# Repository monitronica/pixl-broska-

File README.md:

# Pixl Broška — A Wearable Programmable Pixel Brooch

**A project by monitronica**

> Twenty LEDs, one tiny microcontroller, and a wearable space for words, images, and motion.

Official project visuals: [finished brooch and circuit-board close-up](https://radiona.org/monika-pocrnjic-radionica-pikslbroska/) · [workshop documentation](https://kons-platforma.org/en/dogodki/pixelbrooch-6/)

The official sources do not state a reusable image license, so photographs are linked rather than copied. See [image credits and permission status](images/README.md).

## Project overview

Pixl Broška is a programmable electronic brooch with a hand-built 4×5 LED display. Its twenty large “pixels” can show scrolling words, simple drawings, symbols, and short frame-by-frame animations. Worn on clothing, the circuit becomes a small public screen: part accessory, part message board, and part introduction to creative coding.

The project is designed for experimentation. A first-time maker can solder a working object and start by changing a line of text, while a more experienced participant can draw new bitmap characters, design animation frames, or rewrite the display routine.

## Artistic concept and background

Clothing and jewelry already communicate identity, mood, and belonging. Pixl Broška makes that communication programmable. Instead of fixing one image or slogan permanently, the wearer can decide what the object says today, how it moves, and when it says nothing at all.

Its visible circuitry is part of the work. The grid of individual LEDs gives digital imagery a physical scale, while the circuit board places code, electronics, and personal expression directly on the body. The limited resolution encourages the visual economy of pixel art: every light matters.

Pixl Broška was the first workshop developed within the Maribor part of the konS platform. The first documented online edition took place in December 2020, when participants received material kits at home. Later workshops brought the project to students, children, young people, and adult beginners in Maribor, Novo Mesto, Velenje, Zagreb, and other konS partner locations.

## Inspiration & Acknowledgements

Pixl Broška was inspired by **benbrandt22** and the Instructables project [*Creating a Charlieplexed LED Grid to Run on ATTiny85*](https://www.instructables.com/Creating-a-charlieplexed-LED-grid-to-run-on-ATTiny/). Building on that generous sharing of knowledge, design, code, and inspiration, **monitronica** redesigned and created a new PCB, adapted and modified parts of the original code, and developed a distinct wearable artistic interpretation of the project.

Warm thanks to [benbrandt22](https://www.instructables.com/member/benbrandt22/) for making the original project available to fellow makers. No text, photographs, or other media from the Instructables page are reproduced here; the original material remains subject to the copyright and licensing terms of its author and source platform.

## How Pixl Broška works

The brooch uses an **ATtiny85V**, a low-power 8-bit AVR microcontroller, to control a matrix of **twenty 5 mm LEDs** arranged as four columns by five rows.

Five microcontroller pins drive the display through **charlieplexing**. Each LED sits between a different ordered pair of pins. The firmware repeatedly changes selected pins between high, low, and high-impedance input states, lighting one LED path at a time. This scanning happens quickly enough for the separate points of light to appear as a complete image.

The repository contains two display approaches:

- [`srce1.ino`](srce1.ino) stores a sequence of 4×5 bitmap frames and plays them as a short animation.
- [`PixlBroskaTekst.ino`](PixlBroskaTekst.ino) defines a compact bitmap alphabet and scrolls a programmed text string across the display.

The result is deliberately small and direct: no phone, wireless connection, or separate screen is required once the firmware has been uploaded.

## Hardware and electronics

The repository's board and bill of materials specify:

- 1 × ATtiny85V-10PU microcontroller in an 8-pin DIP package
- 1 × DIP-8 socket
- 20 × 5 mm through-hole LEDs
- 5 × 100 Ω through-hole resistors
- 1 × CR2032 3 V coin cell and through-hole holder
- 1 × SPDT slide switch for power
- 1 × six-pin ISP programming header
- a custom two-layer KiCad PCB that forms the body of the brooch

The six-pin header exposes the standard AVR programming connections: MISO, MOSI, SCK, reset, power, and ground. The CR2032 holder sits on the rear of the board, while the LED matrix and visible controls form the front-facing display.

This is **wearable electronics**, not an electronic-textile circuit: the electronics are assembled on a rigid PCB and worn on clothing rather than sewn with conductive thread or integrated into fabric.

## Programming and animation

The included sketches use Arduino-style C/C++ and can be adapted in the Arduino development environment with an ATtiny85-compatible core and an AVR ISP programmer. An Arduino configured as an ISP can also be used when set up correctly. Confirm the selected ATtiny core, clock, fuse, and programmer settings before uploading.

### Change the scrolling text

In [`PixlBroskaTekst.ino`](PixlBroskaTekst.ino), edit the message constant:

```cpp
#define PRIKAZI_BESEDILO " HELLO WORLD "
```

The sketch maps letters, digits, spaces, and a few lowercase characters to 4×5 bitmaps, then moves the message across the LED grid. The `HITROST` value controls the scrolling speed.

### Draw an animation

In [`srce1.ino`](srce1.ino), each frame is five rows of four bits:

```cpp
{ 0b0000,
  0b0110,
  0b0011,
  0b0110,
  0b0000 }
```

Each `1` represents a lit pixel. Add or replace frames, then adjust the playback loop and duration to change the movement. Simple icons, blinking patterns, faces, and abstract rhythms work especially well at this scale.

## Building your own brooch

1. Review the [BOM](pikselbroska1.csv), [PCB layout](pikselbroska.kicad_pcb), and firmware before ordering parts or boards.
2. Fabricate the PCB from the KiCad source or the archived Gerber and drill files in [`BroskaPiksL.rar`](BroskaPiksL.rar). Verify the fabrication outputs with your board manufacturer before ordering.
3. Sort and identify every component. Check LED polarity and the orientation marks for the DIP socket, ATtiny85, battery holder, switch, and ISP header.
4. Solder the lowest-profile parts first, typically the resistors and socket, followed by the LEDs, header, switch, and battery holder.
5. Inspect every joint and test for shorts before inserting the microcontroller or battery.
6. Upload a simple display test through the ISP header, then program the scrolling-text or animation sketch.
7. Fit the brooch securely to clothing so that conductive parts cannot contact skin, loose metal, or other conductive objects.

Work in a ventilated area, use eye protection when trimming leads, and keep the soldering iron in a stable stand. Coin cells are hazardous if swallowed and must be kept away from small children and stored safely. Beginners should build with an experienced facilitator.

## Project photographs

Authentic Pixl Broška images are available from the official project and workshop pages:

| View | Official source | Permission status |
| --- | --- | --- |
| Finished brooch shown on clothing | [Radiona workshop page](https://radiona.org/monika-pocrnjic-radionica-pikslbroska/) | Reuse license not stated; linked only |
| Populated board, LED display, and rear battery holder | [Radiona workshop page](https://radiona.org/monika-pocrnjic-radionica-pikslbroska/) | Reuse license not stated; linked only |
| Workshop and event documentation | [konS PixeLBrooch](https://kons-platforma.org/en/dogodki/pixelbrooch-6/) and [MKC Maribor](https://mkc.si/koledar/2020/12/16/kons-delavnica-pikslbroska) | Reuse license not established; linked only |

No photograph has been copied into this repository without confirmed permission. Candidate-image details are documented in [`images/README.md`](images/README.md).

## Workshops and educational context

Pixl Broška turns a wearable object into an approachable lesson in electronics and programming. Workshop participants encounter:

- safe soldering and component orientation
- current-limiting resistors and LED polarity
- microcontrollers and firmware
- charlieplexing and persistence of vision
- bitmap fonts, binary patterns, and animation frames
- debugging through inspection, continuity testing, and small code changes
- wearable objects as media for public and personal expression

The workshop has been presented for learners with no previous electronics experience. Documented editions include the first online konS workshop in December 2020, a two-part soldering and programming workshop for Maribor students in May and June 2021, konS workshops during 2021–2023, and a Radiona workshop in Zagreb on 12 June 2023.

## Credits and acknowledgements

- **Project and artistic direction:** monitronica
- **Original workshop development:** monitronica, with assistance from Denis Lederhas, Klemen Šali, and Marko Lük
- **Workshop development and production context:** MKC Maribor and konS – Platform for Contemporary Investigative Art
- **2023 Zagreb workshop host:** Radiona – Zagreb Makerspace
- **Radiona page portrait photography:** Gregor Salobir for konSekvence; the portrait is not reproduced in this repository
- **Participating workshop hosts and partners:** konS partner organizations and local venues credited on the linked event pages

Historical source pages may identify monitronica under an earlier/legal-name credit. This repository uses the artist's requested public name while retaining direct source links and the names of collaborators, photographers, and institutions.

## Technical resources and useful links

### Repository files

- [Scrolling-text firmware](PixlBroskaTekst.ino)
- [Frame-animation firmware](srce1.ino)
- [Bill of materials](pikselbroska1.csv)
- [KiCad PCB layout](pikselbroska.kicad_pcb)
- [Legacy KiCad project file](pikselbroska.pro)
- [Archived Gerber and drill files](BroskaPiksL.rar)

### Project and workshop sources

- [PixeLBrooch workshop, konS](https://kons-platforma.org/en/dogodki/pixelbrooch-6/)
- [Pixl Broška workshop, Radiona Zagreb](https://radiona.org/monika-pocrnjic-radionica-pikslbroska/)
- [Pixl Broška workshop overview, MKC Maribor](https://mkc.si/park-delavnice)
- [First online Pixl Broška workshop, MKC Maribor](https://mkc.si/koledar/2020/12/16/kons-delavnica-pikslbroska)
- [2021 soldering workshop announcement, Kultura Maribor](https://kultura.maribor.si/dogodek/kons-mb-x-kms-delavnica-pikslbroska-spajkanje/)
- [2021 programming workshop announcement, Kultura Maribor](https://kultura.maribor.si/dogodek/kons-mb-x-kms-delavnica-pikslbroska-programiranje/)
- [ATtiny85 product page, Microchip](https://www.microchip.com/en-us/product/attiny85)
- [monitronica on GitHub](https://github.com/monitronica)

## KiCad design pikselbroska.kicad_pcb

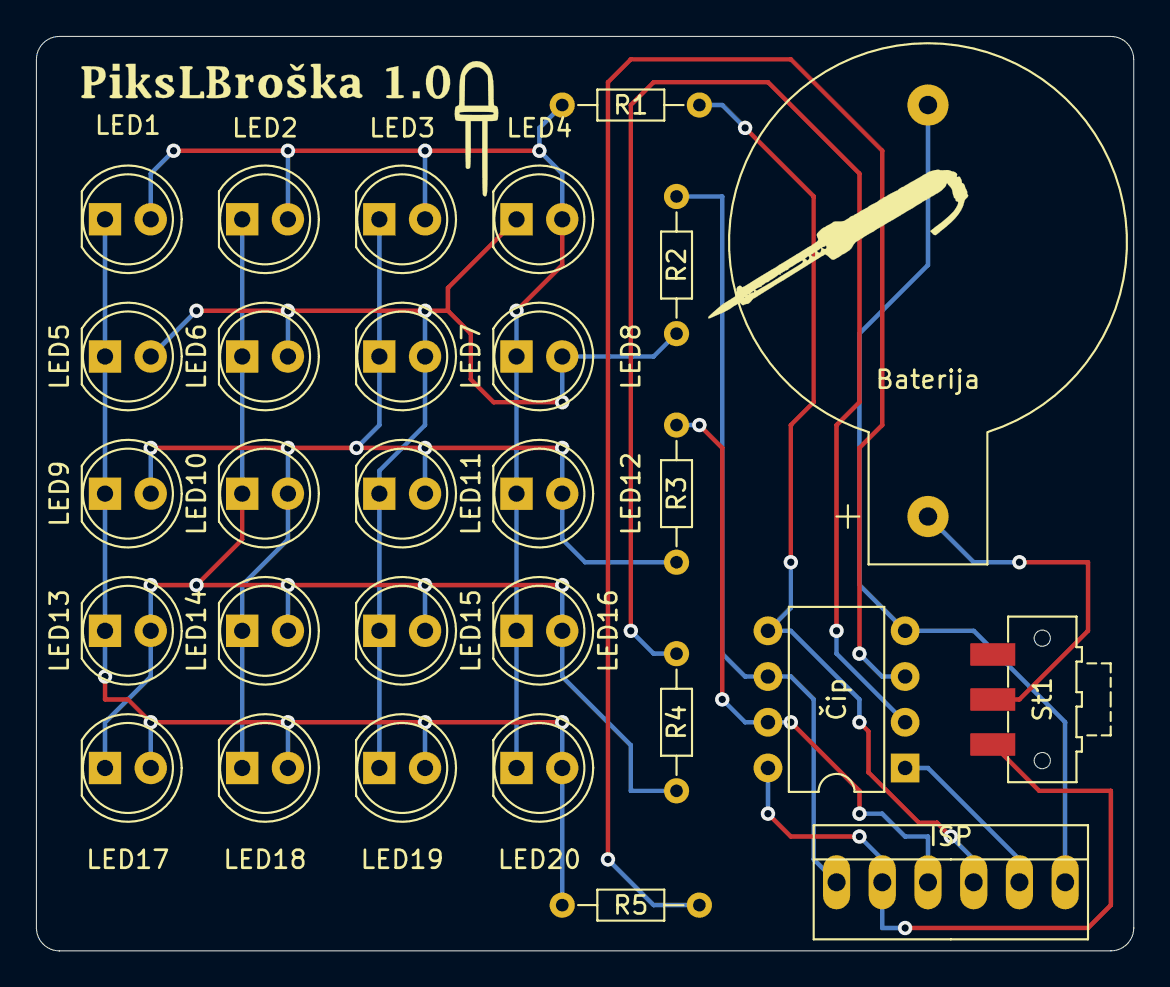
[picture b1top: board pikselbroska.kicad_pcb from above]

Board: 2 copper layers, 61.0 x 50.8 mm, 29 parts (0 on the bottom side), 13 nets.

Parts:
Baterija: BT1; CR2032H
ISP: 6 pin connector ISP; PINHEAD1-6
LED1, LED2, LED3, LED4, LED5, LED6, LED7, LED8, LED9, LED10, LED11, LED12, LED13, LED14, LED15, LED16, LED17, LED18, LED19, LED20: 5mm; LED_D5.0mm
R1, R2, R3, R4, R5: 100; R_Axial_DIN0204_L3.6mm_D1.6mm_P7.62mm_Horizontal
St1: SW_DIP_x01; SW_SPDT_CK-JS102011SAQN
Čip: ATtiny85V-10PU; DIP-8_W7.62mm

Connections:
GND: Baterija.2, ISP.6, Čip.4
MISO: ISP.1, R2.1, Čip.6
MOSI: ISP.4, R1.1, Čip.5
unnamed: LED1.1, LED5.1, LED9.1, LED13.1, LED17.2, LED18.2, LED19.2, LED20.2, R5.2
unnamed: LED1.2, LED2.2, LED3.2, LED4.2, LED8.1, LED12.1, LED16.1, LED20.1, R1.2
unnamed: LED2.1, LED6.1, LED10.1, LED13.2, LED14.2, LED15.2, LED16.2, LED17.1, R4.2
unnamed: LED3.1, LED7.1, LED9.2, LED10.2, LED11.2, LED12.2, LED14.1, LED18.1, R3.2
unnamed: LED4.1, LED5.2, LED6.2, LED7.2, LED8.2, LED11.1, LED15.1, LED19.1, R2.2
PB3: R4.1, Čip.2
PB4: R5.1, Čip.3
RST: ISP.5, Čip.1
SCK: ISP.3, R3.1, Čip.7
VCC: Baterija.1, ISP.2, St1.1, St1.2, Čip.8

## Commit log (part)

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2021-02-11 Modify code
    Add your text here:
    #define PRIKAZI_BESEDILO "Hello world"
    change speed of text/ edit number:
    #define HITROST 1
    add or remove characters, design your own animation:
    Znk('A', 0b10011001111110010110);
2021-02-11 edit instructions
    First version of build and program instructions for pikslboška pcb
